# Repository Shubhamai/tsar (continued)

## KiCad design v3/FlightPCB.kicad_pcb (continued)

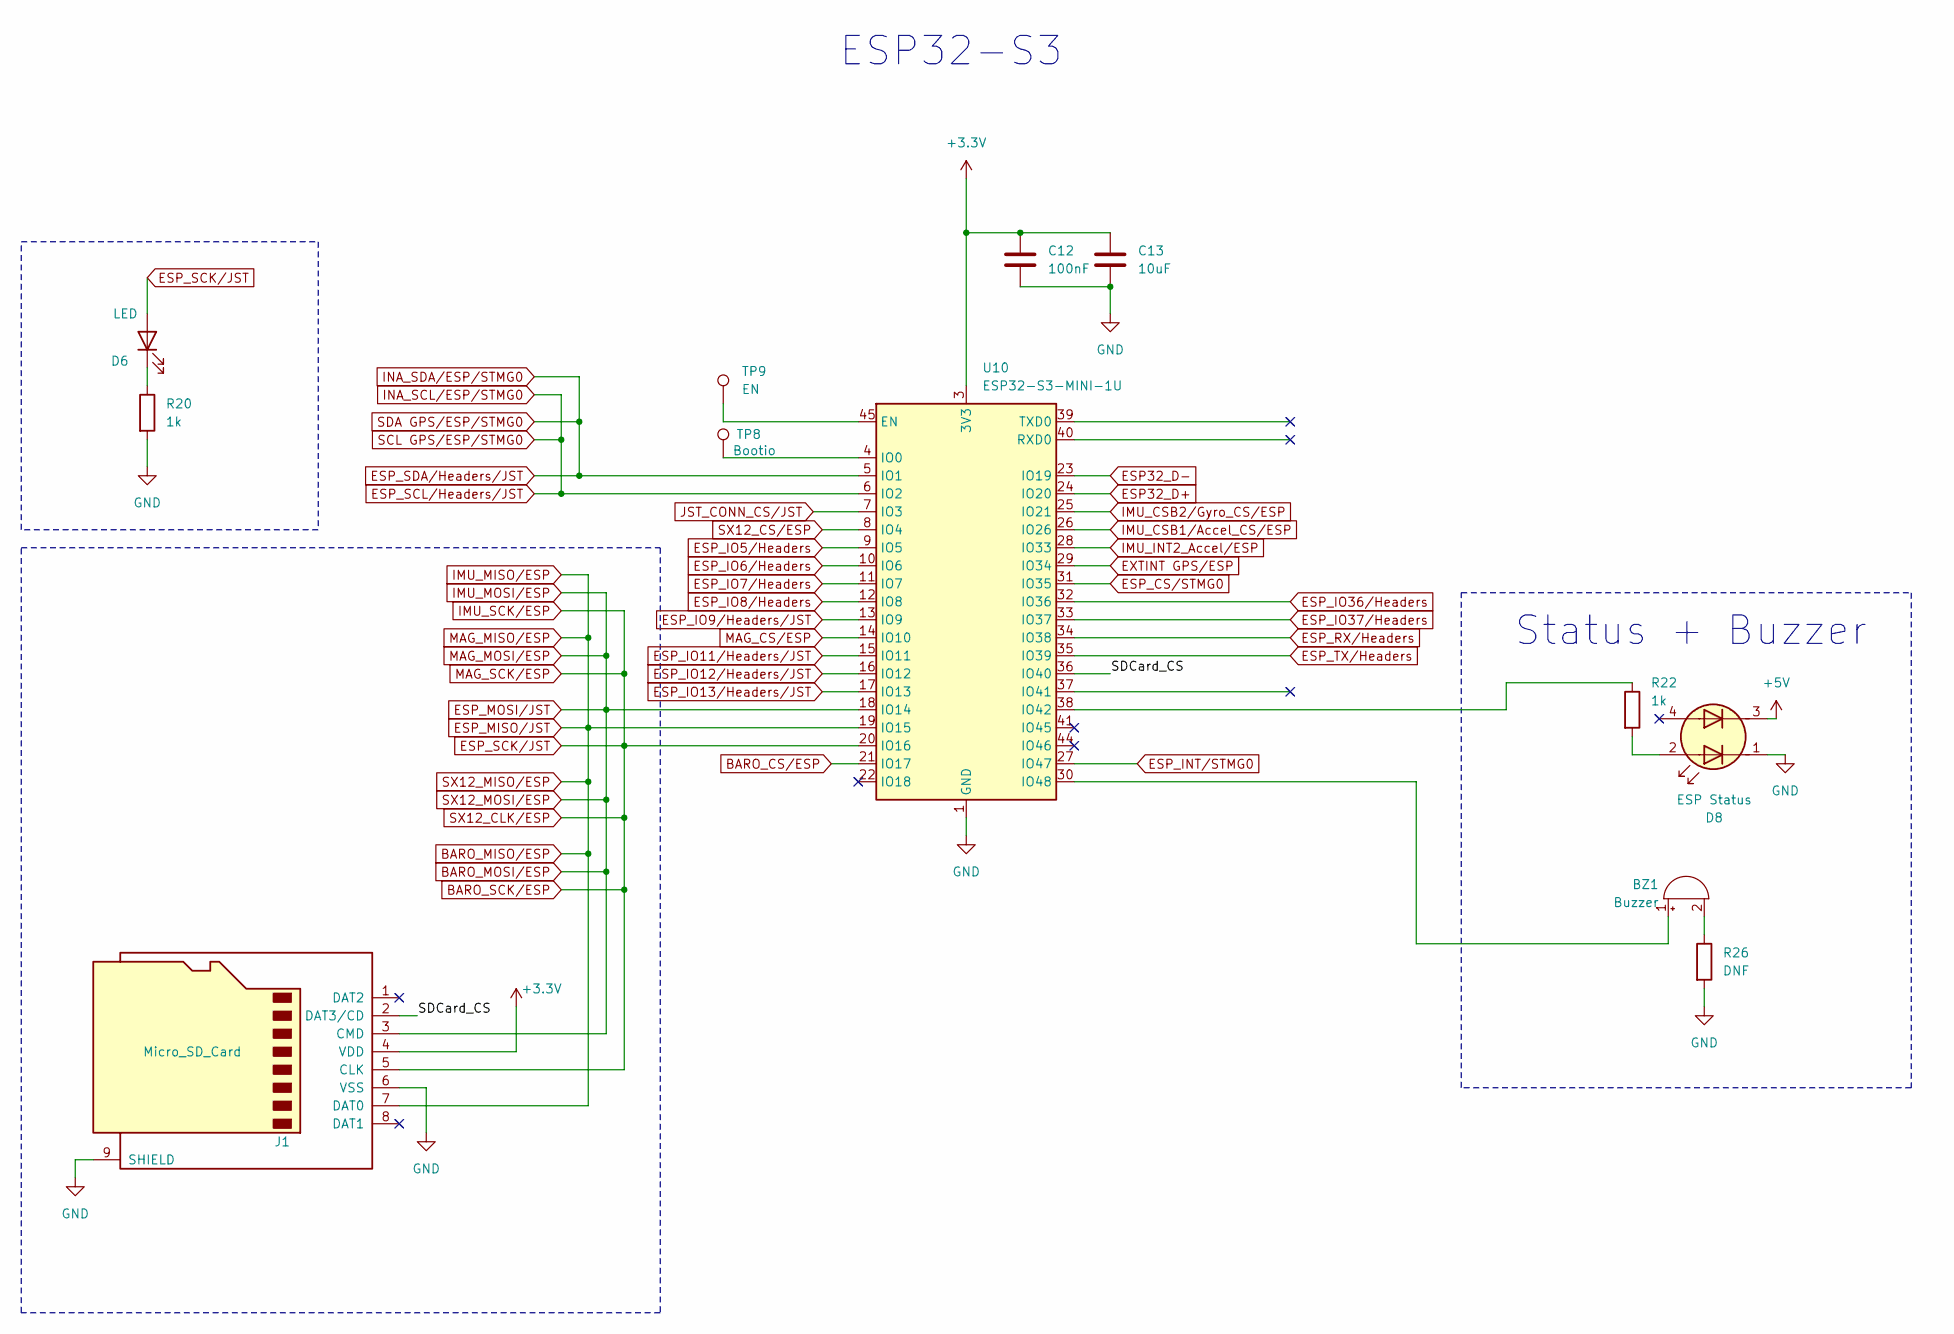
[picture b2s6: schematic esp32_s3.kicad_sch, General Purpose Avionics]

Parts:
BZ1: Buzzer; Buzzer_CUI_CPT-9019S-SMT
C12: 100nF; C_0603_1608Metric
C13: 10uF; C_0603_1608Metric
D6: LED; LED_0402_1005Metric
D8: ESP Status; IN-PI22TAT5R5G5B
J1: Micro_SD_Card; microSD_HC_Molex_47219-2001
R20, R22: 1k; R_0402_1005Metric
R26: DNF; R_0402_1005Metric
TP8: Bootio; TestPoint_Pad_D1.0mm
TP9: EN; TestPoint_Pad_D1.0mm
U10: ESP32-S3-MINI-1U; ESP32-S2-MINI-1U

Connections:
+3.3V: C12.1, C13.1, J1.4 (VDD), U10.3 (3V3); also elsewhere on the board
+5V: D8.3 (A2); also elsewhere on the board
/esp32_s3/SDCard_CS: J1.2 (DAT3/CD), U10.36 (IO40)
BARO_CS/ESP: U10.21 (IO17); also elsewhere on the board
BARO_MISO/ESP: J1.7 (DAT0), U10.19 (IO15); also elsewhere on the board
BARO_MOSI/ESP: J1.3 (CMD), U10.18 (IO14); also elsewhere on the board
BARO_SCK/ESP: D6.2 (A), J1.5 (CLK), U10.20 (IO16); also elsewhere on the board
BatteryTerminal-: C12.2, C13.2, D8.1 (A1), J1.6 (VSS), J1.9 (SHIELD), R20.2, R26.2, U10.1 (GND), U10.2 (GND), U10.42 (GND), U10.43 (GND), U10.46 (GND), U10.47 (GND), U10.48 (GND), U10.49 (GND), U10.50 (GND), U10.51 (GND), U10.52 (GND), U10.53 (GND), U10.54 (GND), U10.55 (GND), U10.56 (GND), U10.57 (GND), U10.58 (GND), U10.59 (GND), U10.60 (GND), U10.61 (GND), U10.62 (GND), U10.63 (GND), U10.64 (GND), U10.65 (GND); also elsewhere on the board
ESP32_D+: U10.24 (IO20); also elsewhere on the board
ESP32_D-: U10.23 (IO19); also elsewhere on the board
ESP_CS/STMG0: U10.31 (IO35); also elsewhere on the board
ESP_INT/STMG0: U10.27 (IO47); also elsewhere on the board
ESP_IO5/Headers: U10.9 (IO5); also elsewhere on the board
ESP_IO6/Headers: U10.10 (IO6); also elsewhere on the board
ESP_IO7/Headers: U10.11 (IO7); also elsewhere on the board
ESP_IO8/Headers: U10.12 (IO8); also elsewhere on the board
ESP_IO9/Headers/JST: U10.13 (IO9); also elsewhere on the board
ESP_IO11/Headers/JST: U10.15 (IO11); also elsewhere on the board
ESP_IO12/Headers/JST: U10.16 (IO12); also elsewhere on the board
ESP_IO13/Headers/JST: U10.17 (IO13); also elsewhere on the board
ESP_IO36/Headers: U10.32 (IO36); also elsewhere on the board
ESP_IO37/Headers: U10.33 (IO37); also elsewhere on the board
ESP_RX/Headers: U10.34 (IO38); also elsewhere on the board
ESP_SCL/Headers/JST: U10.6 (IO2); also elsewhere on the board
ESP_SDA/Headers/JST: U10.5 (IO1); also elsewhere on the board
ESP_TX/Headers: U10.35 (IO39); also elsewhere on the board
EXTINT GPS/ESP: U10.29 (IO34); also elsewhere on the board
IMU_CSB1/Accel_CS/ESP: U10.26 (IO26); also elsewhere on the board
IMU_CSB2/Gyro_CS/ESP: U10.25 (IO21); also elsewhere on the board
IMU_INT2_Accel/ESP: U10.28 (IO33); also elsewhere on the board
JST_CONN_CS/JST: U10.7 (IO3); also elsewhere on the board
MAG_CS/ESP: U10.14 (IO10); also elsewhere on the board
unnamed: BZ1.1 (+), U10.30 (IO48)
unnamed: BZ1.2 (-), R26.1
unnamed: D6.1 (K), R20.1
unnamed: D8.2 (K1), R22.2
unnamed: TP9.1, U10.45 (EN)
unnamed: TP8.1, U10.4 (IO0)
unnamed: R22.1, U10.38 (IO42)
SX12_CS/ESP: U10.8 (IO4); also elsewhere on the board

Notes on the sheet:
Status + Buzzer
ESP32-S3

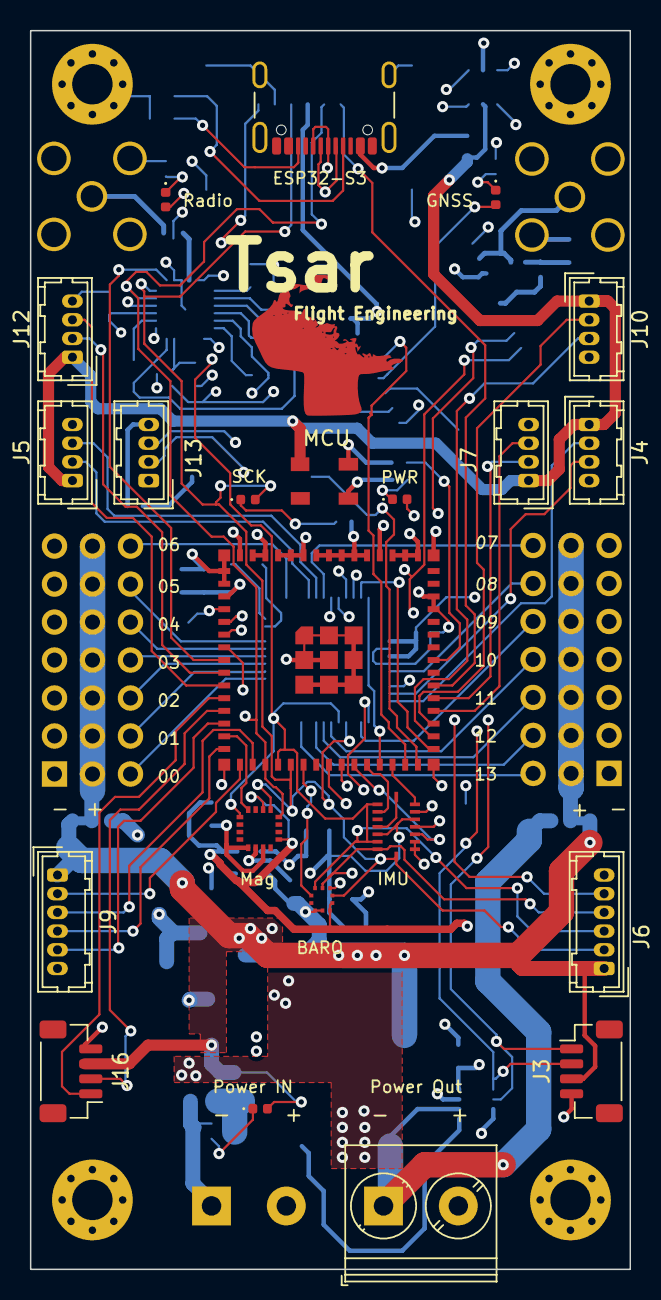
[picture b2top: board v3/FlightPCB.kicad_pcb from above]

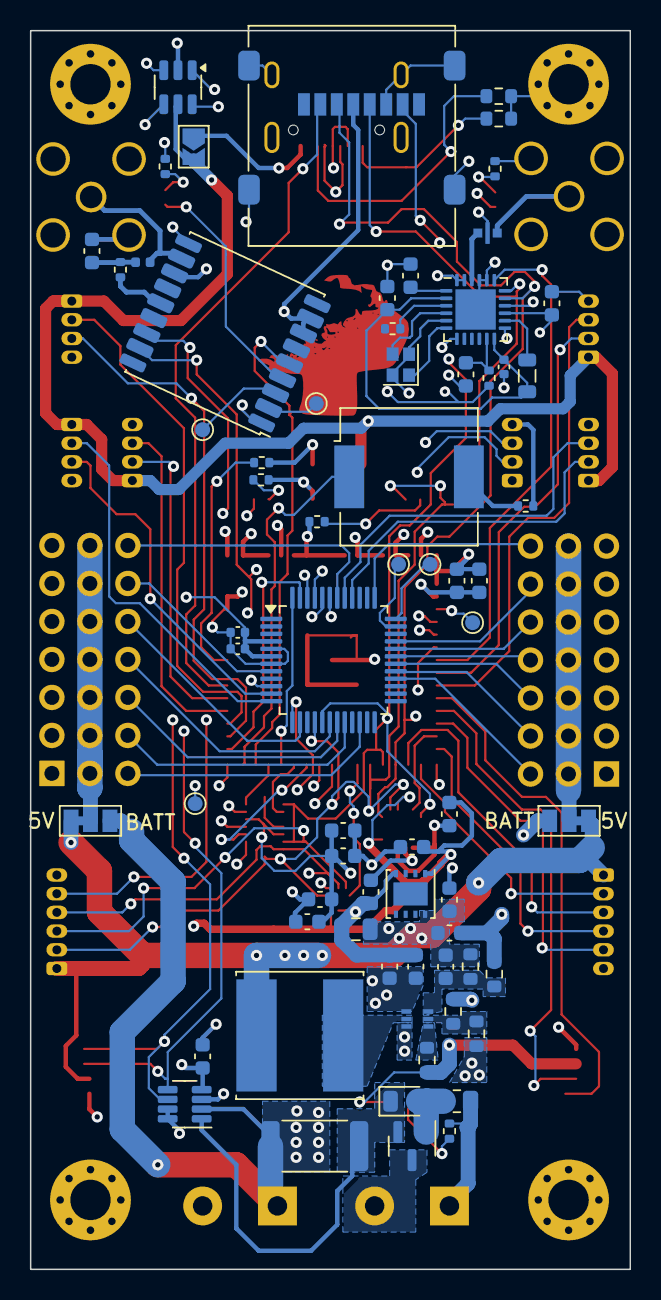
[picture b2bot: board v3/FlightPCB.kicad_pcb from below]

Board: 4 copper layers, 40.1 x 82.8 mm, 99 parts (68 on the bottom side), 99 nets.

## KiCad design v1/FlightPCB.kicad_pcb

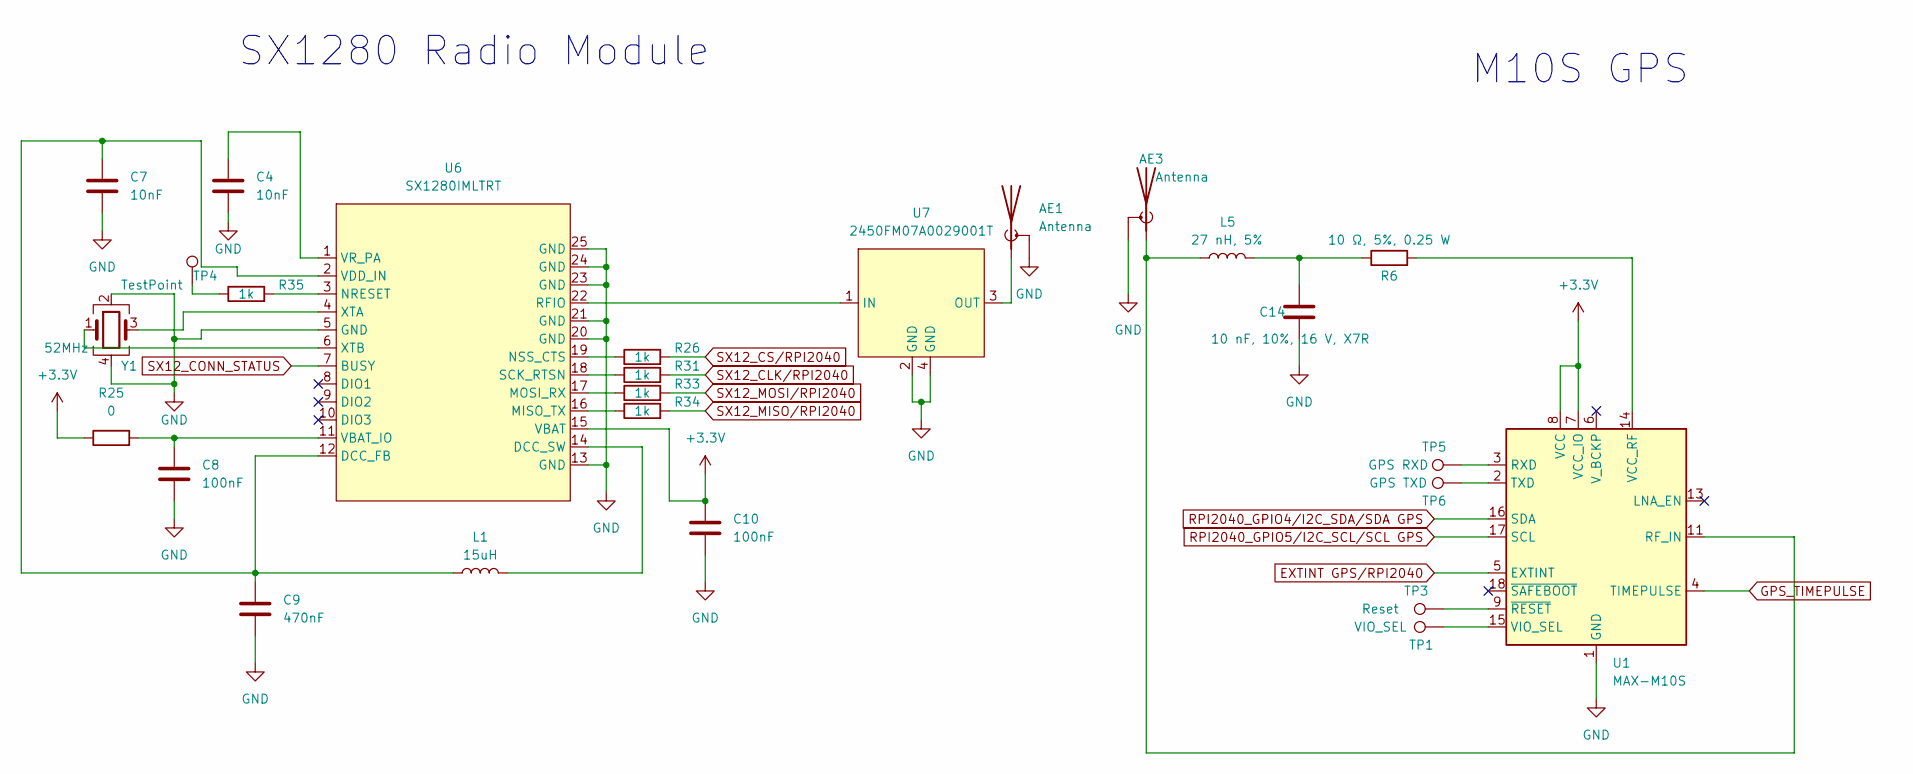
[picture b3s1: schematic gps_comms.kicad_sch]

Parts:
AE1, AE3: Antenna; SMA_Amphenol_901-144_Vertical
C4, C7: 10nF; C_0402_1005Metric
C8, C10: 100nF; C_0402_1005Metric
C9: 470nF; C_0402_1005Metric
C14: 10 nF, 10%, 16 V, X7R; C_0603_1608Metric
L1: 15uH; L_0805_2012Metric
L5: 27 nH, 5%; L_0402_1005Metric
R6: 10 Ω, 5%, 0.25 W; R_0402_1005Metric
R25: 0; R_0402_1005Metric
R26, R31, R33, R34, R35: 1k; R_0402_1005Metric
TP1: VIO_SEL; TestPoint_Pad_D1.0mm
TP3: Reset; TestPoint_Pad_D1.0mm
TP4: TestPoint; TestPoint_Pad_D1.0mm
TP5: GPS RXD; TestPoint_Pad_D1.0mm
TP6: GPS TXD; TestPoint_Pad_D1.0mm
U1: MAX-M10S; ublox_MAX
U6: SX1280IMLTRT; QFN-24-1EP_4x4mm_P0.5mm_EP2.7x2.7mm
U7: 2450FM07A0029001T
Y1: 52MHz; Crystal_SMD_2016-4Pin_2.0x1.6mm

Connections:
+3.3V: C10.1, R25.1, U1.7 (VCC_IO), U1.8 (VCC), U6.15 (VBAT); also elsewhere on the board
BatteryTerminal-: AE1.2 (Shield), AE3.2 (Shield), C4.2, C7.2, C8.2, C9.2, C10.2, C14.1, U1.1 (GND), U1.10 (GND), U1.12 (GND), U6.5 (GND), U6.13 (GND), U6.20 (GND), U6.21 (GND), U6.23 (GND), U6.24 (GND), U6.25 (GND), U7.2 (GND), U7.4 (GND), Y1.2, Y1.4; also elsewhere on the board
EXTINT GPS/RPI2040: U1.5 (EXTINT); also elsewhere on the board
GPS_TIMEPULSE: U1.4 (TIMEPULSE); also elsewhere on the board
INA_SCL_RPI2040: U1.17 (SCL); also elsewhere on the board
INA_SDA_RPI2040: U1.16 (SDA); also elsewhere on the board
unnamed: AE1.1 (A), U7.3 (OUT)
unnamed: AE3.1 (A), L5.1, U1.11 (RF_IN)
unnamed: C14.2, L5.2, R6.1
unnamed: R35.1, TP4.1
unnamed: TP5.1, U1.3 (RXD)
unnamed: TP6.1, U1.2 (TXD)
unnamed: R6.2, U1.14 (VCC_RF)
unnamed: TP1.1, U1.15 (VIO_SEL)
unnamed: TP3.1, U1.9 (~RESET)
unnamed: C7.1, C9.1, L1.1, U6.2 (VDD_IN), U6.12 (DCC_FB)
unnamed: L1.2, U6.14 (DCC_SW)
unnamed: R34.1, U6.16 (MISO_TX)
unnamed: R33.1, U6.17 (MOSI_RX)
unnamed: R35.2, U6.3 (NRESET)
unnamed: R26.1, U6.19 (NSS_CTS)
unnamed: U6.22 (RFIO), U7.1 (IN)
unnamed: R31.1, U6.18 (SCK_RTSN)
unnamed: C8.1, R25.2, U6.11 (VBAT_IO)
unnamed: C4.1, U6.1 (VR_PA)
unnamed: U6.4 (XTA), Y1.3
unnamed: U6.6 (XTB), Y1.1
RPI2040_GPIO16/MISO/SPI_PIN: R34.2; also elsewhere on the board
RPI2040_GPIO18/SCK/SPI_PIN: R31.2; also elsewhere on the board
RPI2040_GPIO19/MOSI/SPI_PIN: R33.2; also elsewhere on the board
SX12_CONN_STATUS: U6.7 (BUSY); also elsewhere on the board
SX12_CS/RPI2040: R26.2; also elsewhere on the board

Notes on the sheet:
M10S GPS
SX1280 Radio Module

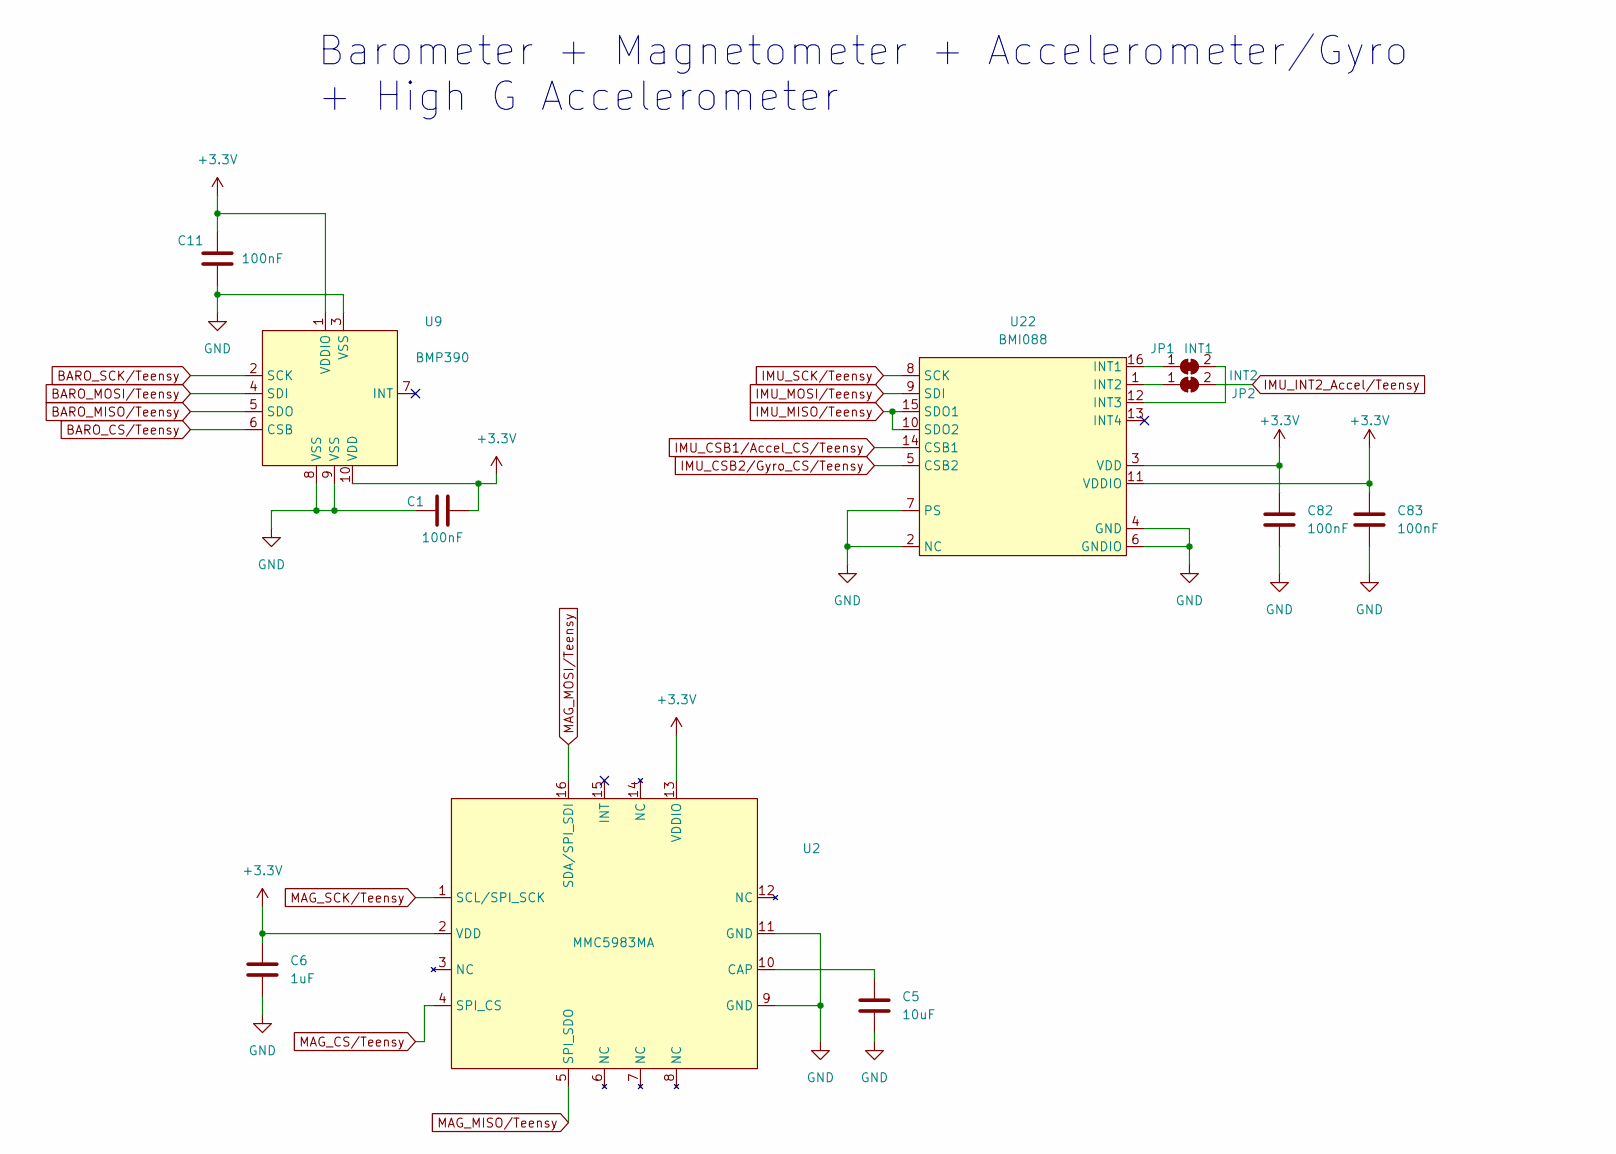
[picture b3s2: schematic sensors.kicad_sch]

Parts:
C1, C11, C82, C83: 100nF; C_0603_1608Metric
C5: 10uF; C_0805_2012Metric
C6: 1uF; C_0603_1608Metric
JP1: INT1; SolderJumper-2_P1.3mm_Bridged_Pad1.0x1.5mm
JP2: INT2; SolderJumper-2_P1.3mm_Bridged_Pad1.0x1.5mm
U2: MMC5983MA
U9: BMP390
U22: BMI088

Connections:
+3.3V: C1.2, C6.1, C11.2, C82.1, C83.1, U2.2 (VDD), U2.13 (VDDIO), U9.1 (VDDIO), U9.10 (VDD), U22.3 (VDD), U22.11 (VDDIO); also elsewhere on the board
BARO_CS/Teensy: U9.6 (CSB); also elsewhere on the board
BARO_MISO/Teensy: U2.5 (SPI_SDO), U9.5 (SDO), U22.10 (SDO2), U22.15 (SDO1); also elsewhere on the board
BARO_MOSI/Teensy: U2.16 (SDA/SPI_SDI), U9.4 (SDI), U22.9 (SDI); also elsewhere on the board
BARO_SCK/Teensy: U2.1 (SCL/SPI_SCK), U9.2 (SCK), U22.8 (SCK); also elsewhere on the board
BatteryTerminal-: C1.1, C5.2, C6.2, C11.1, C82.2, C83.2, U2.9 (GND), U2.11 (GND), U9.3 (VSS), U9.8 (VSS), U9.9 (VSS), U22.2 (NC), U22.4 (GND), U22.6 (GNDIO), U22.7 (PS); also elsewhere on the board
IMU_CSB1/Accel_CS/Teensy: U22.14 (CSB1); also elsewhere on the board
IMU_CSB2/Gyro_CS/Teensy: U22.5 (CSB2); also elsewhere on the board
IMU_INT2_Accel/Teensy: JP2.2 (B); also elsewhere on the board
MAG_CS/Teensy: U2.4 (SPI_CS); also elsewhere on the board
unnamed: JP1.1 (A), U22.16 (INT1)
unnamed: JP1.2 (B), U22.12 (INT3)
unnamed: JP2.1 (A), U22.1 (INT2)
unnamed: C5.1, U2.10 (CAP)

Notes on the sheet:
Barometer + Magnetometer + Accelerometer/Gyro + High G Accelerometer

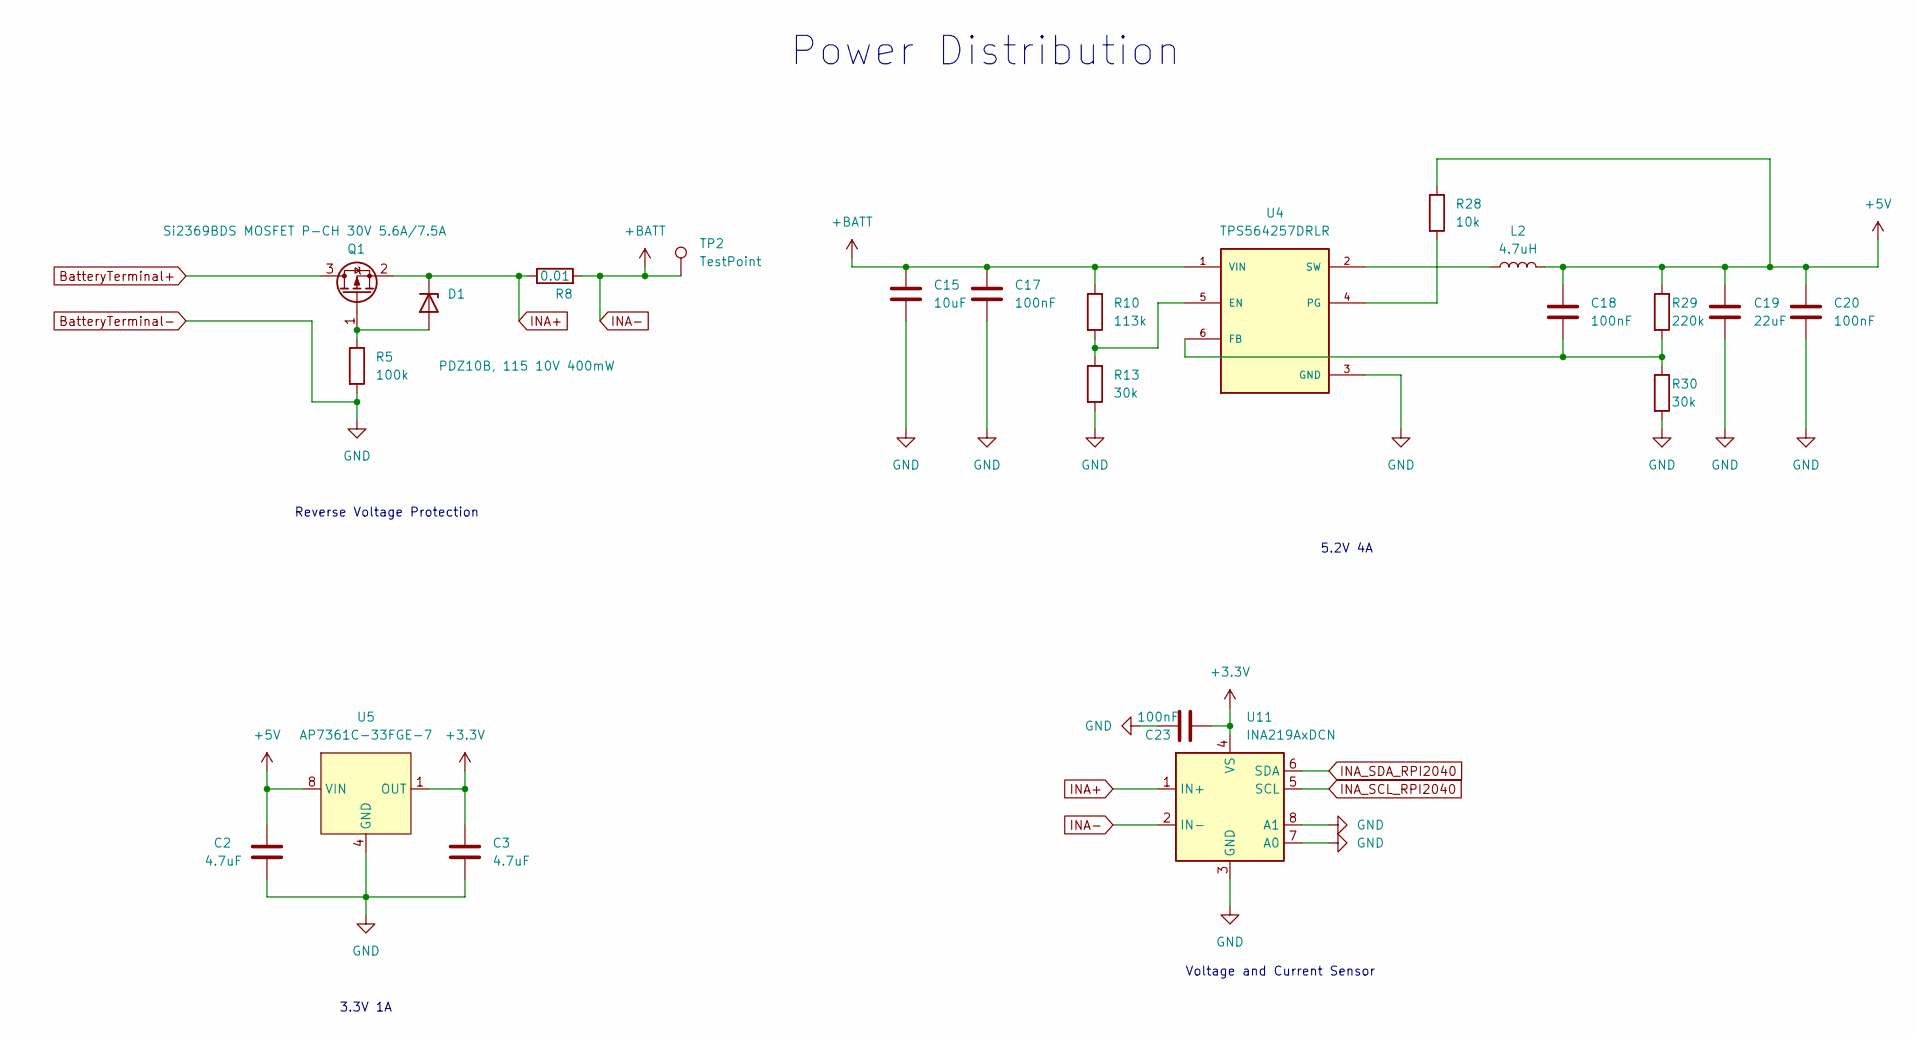
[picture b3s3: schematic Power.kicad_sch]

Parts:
C2, C3: 4.7uF; C_0603_1608Metric
C15: 10uF; C_0805_2012Metric
C17, C18, C20, C23: 100nF; C_0603_1608Metric
C19: 22uF; C_0805_2012Metric
D1: PDZ10B, 115 10V 400mW; D_0805_2012Metric
L2: 4.7uH; L_0805_2012Metric
Q1: Si2369BDS MOSFET P-CH 30V 5.6A/7.5A; SOT-23
R5: 100k; R_0805_2012Metric
R8: 0.01; R_2512_6332Metric
R10: 113k; R_0603_1608Metric
R13, R30: 30k; R_0603_1608Metric
R28: 10k; R_0603_1608Metric
R29: 220k; R_0603_1608Metric
TP2: TestPoint; TestPoint_Pad_D1.0mm
U4: TPS564257DRLR; SOT50P160X60-6N; PARTREV A
U5: AP7361C-33FGE-7; MLF-8-1EP_3x3mm_P0.65mm_EP1.55x2.3mm
U11: INA219AxDCN; SOT-23-8

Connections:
+3.3V: C3.1, C23.2, U5.1 (OUT), U11.4 (VS); also elsewhere on the board
+5V: C2.1, C18.1, C19.1, C20.1, L2.2, R28.1, R29.1, U5.8 (VIN); also elsewhere on the board
BatteryTerminal+: Q1.3 (D); also elsewhere on the board
BatteryTerminal-: C2.2, C3.2, C15.2, C17.2, C19.2, C20.2, C23.1, R5.2, R13.2, R30.2, U4.3 (GND), U5.4 (GND), U11.3 (GND), U11.7 (A0), U11.8 (A1); also elsewhere on the board
INA+: D1.1 (K), Q1.2 (S), R8.1, U11.1 (IN+)
INA-: C15.1, C17.1, R8.2, R10.1, TP2.1, U4.1 (VIN), U11.2 (IN-)
INA_SCL_RPI2040: U11.5 (SCL); also elsewhere on the board
INA_SDA_RPI2040: U11.6 (SDA); also elsewhere on the board
unnamed: D1.2 (A), Q1.1 (G), R5.1
unnamed: R10.2, R13.1, U4.5 (EN)
unnamed: C18.2, R29.2, R30.1, U4.6 (FB)
unnamed: R28.2, U4.4 (PG)
unnamed: L2.1, U4.2 (SW)

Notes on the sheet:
Voltage and Current Sensor
3.3V 1A
Reverse Voltage Protection
5.2V 4A
Power Distribution

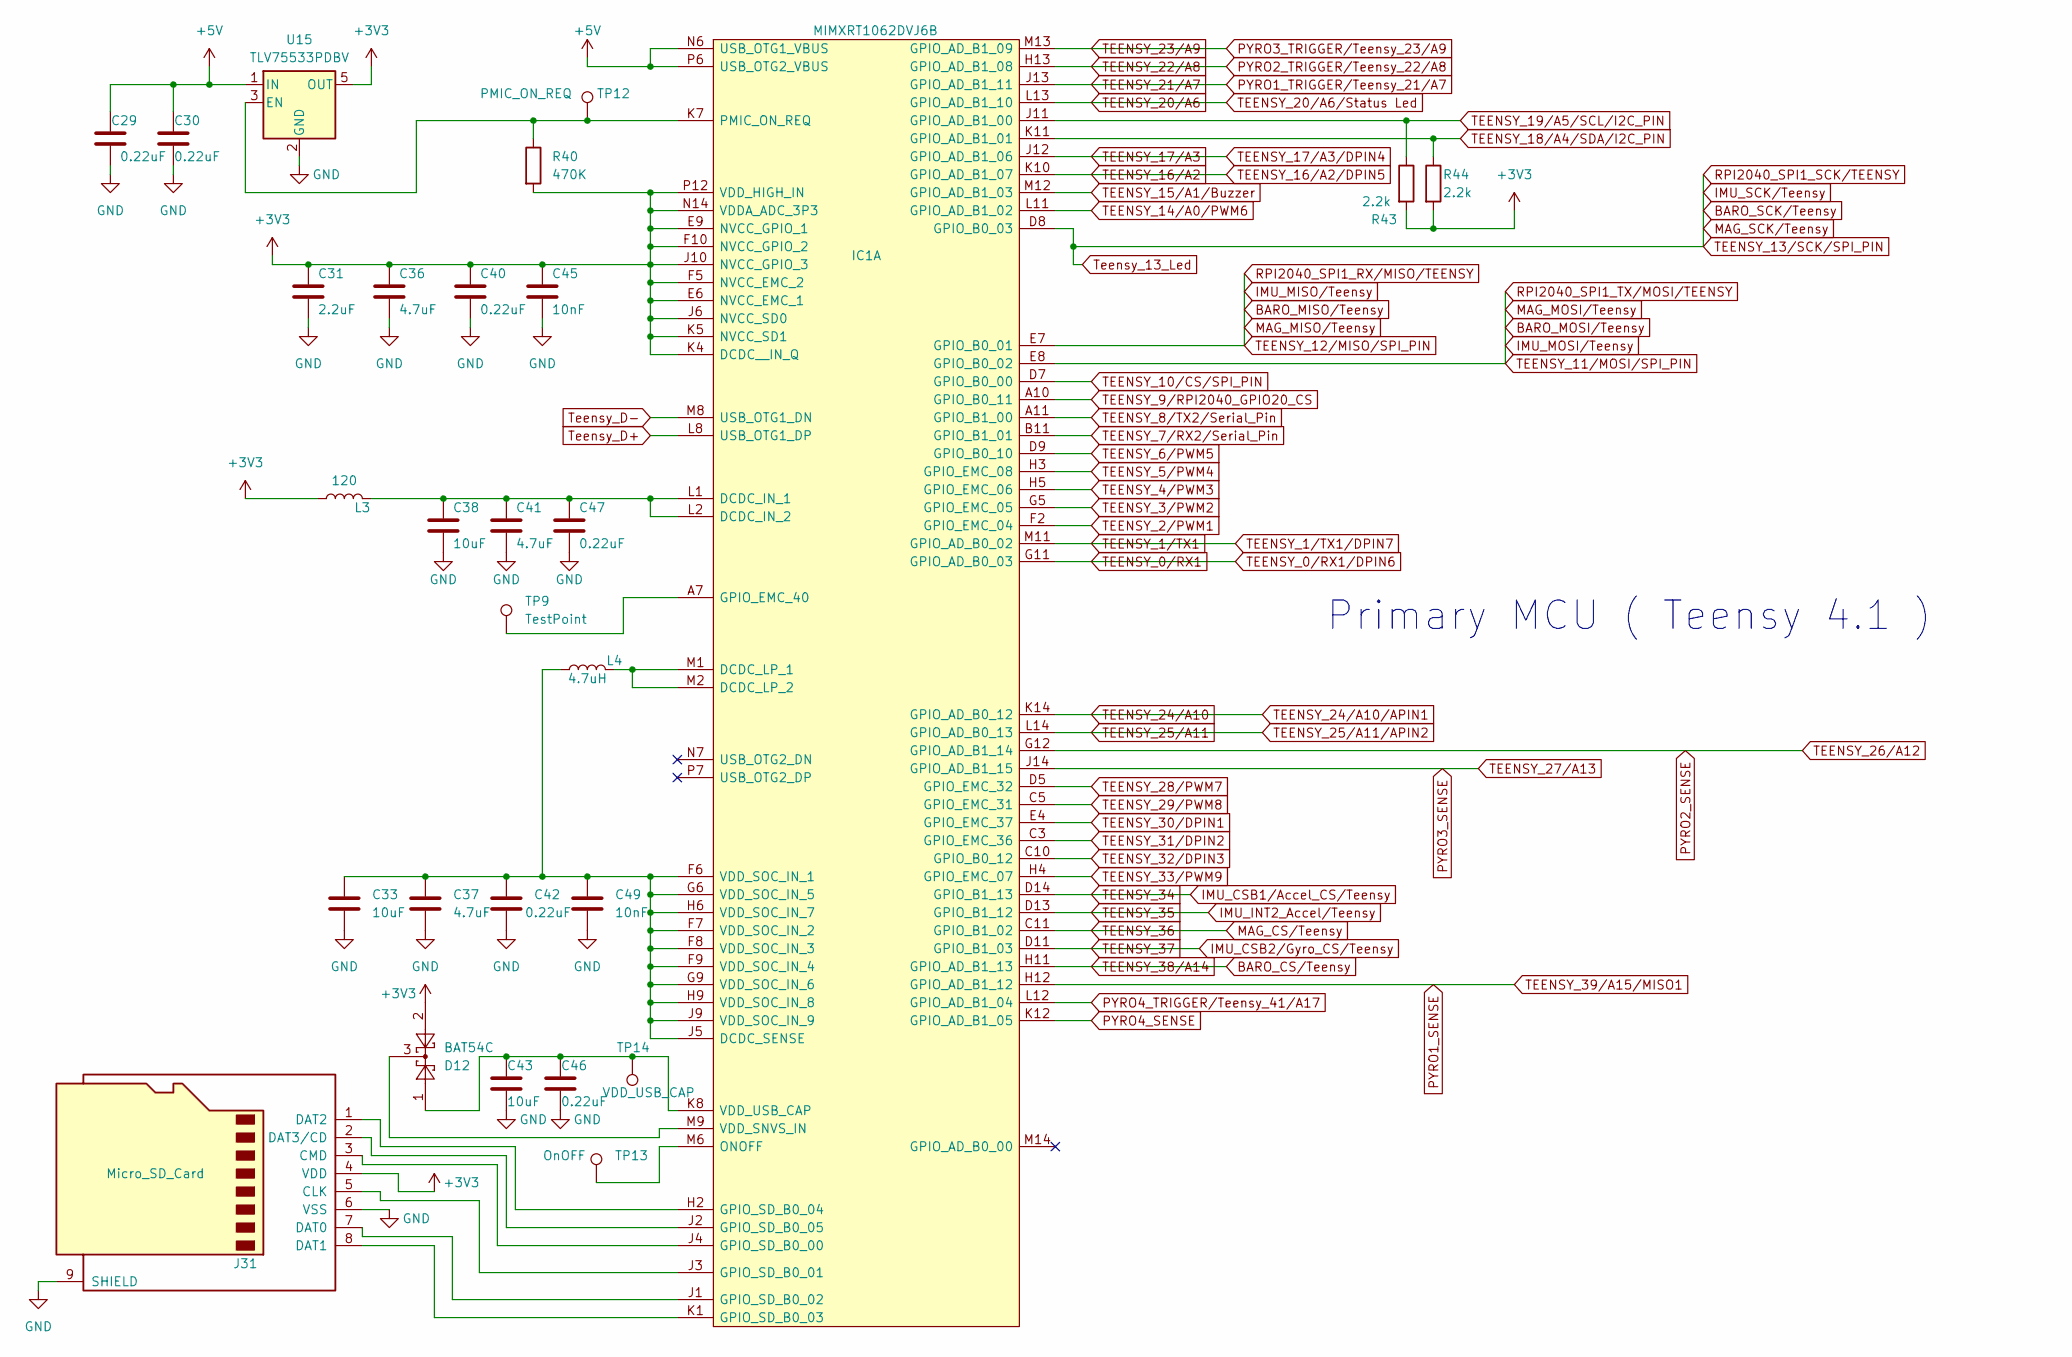
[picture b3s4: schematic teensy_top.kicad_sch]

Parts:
C29, C30, C40, C42, C46, C47: 0.22uF; C_0402_1005Metric
C31: 2.2uF; C_0603_1608Metric
C33, C38, C43: 10uF; C_0603_1608Metric
C36, C37, C41: 4.7uF; C_0603_1608Metric
C45, C49: 10nF; C_0402_1005Metric
D12: BAT54C; SOT-23
IC1: MIMXRT1062DVJ6B; BGA196C80P14X14_1200X1200X152; Mouser Part Number 771-MIMXRT1062DVJ6B
J31: Micro_SD_Card; microSD_HC_Molex_47219-2001
L3: 120; L_0805_2012Metric
L4: 4.7uH; L_0805_2012Metric
R40: 470K; R_0603_1608Metric
R43, R44: 2.2k; R_0603_1608Metric
TP9: TestPoint; TestPoint_Pad_D1.0mm
TP12: PMIC_ON_REQ; TestPoint_Pad_D1.0mm
TP13: OnOFF; TestPoint_Pad_D1.0mm
TP14: VDD_USB_CAP; TestPoint_Pad_D1.0mm
U15: TLV75533PDBV; SOT-23-5

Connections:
+5V: C29.1, C30.1, IC1.N6 (USB_OTG1_VBUS), IC1.P6 (USB_OTG2_VBUS), U15.1 (IN); also elsewhere on the board
BARO_CS/Teensy: IC1.H11 (GPIO_AD_B1_13); also elsewhere on the board
BARO_MISO/Teensy: IC1.E7 (GPIO_B0_01); also elsewhere on the board
BARO_MOSI/Teensy: IC1.E8 (GPIO_B0_02); also elsewhere on the board
BARO_SCK/Teensy: IC1.D8 (GPIO_B0_03); also elsewhere on the board
BatteryTerminal-: C29.2, C30.2, C31.2, C33.2, C36.2, C37.2, C38.2, C40.2, C41.2, C42.2, C43.2, C45.2, C46.2, C47.2, C49.2, J31.6 (VSS), J31.9 (SHIELD), U15.2 (GND); also elsewhere on the board
IMU_CSB1/Accel_CS/Teensy: IC1.D14 (GPIO_B1_13); also elsewhere on the board
IMU_CSB2/Gyro_CS/Teensy: IC1.D11 (GPIO_B1_03); also elsewhere on the board
IMU_INT2_Accel/Teensy: IC1.D13 (GPIO_B1_12); also elsewhere on the board
MAG_CS/Teensy: IC1.C11 (GPIO_B1_02); also elsewhere on the board
unnamed: C38.1, C41.1, C47.1, IC1.L1 (DCDC_IN_1), IC1.L2 (DCDC_IN_2), L3.1
unnamed: IC1.M1 (DCDC_LP_1), IC1.M2 (DCDC_LP_2), L4.2
unnamed: C33.1, C37.1, C42.1, C49.1, IC1.F6 (VDD_SOC_IN_1), IC1.F7 (VDD_SOC_IN_2), IC1.F8 (VDD_SOC_IN_3), IC1.F9 (VDD_SOC_IN_4), IC1.G6 (VDD_SOC_IN_5), IC1.G9 (VDD_SOC_IN_6), IC1.H6 (VDD_SOC_IN_7), IC1.H9 (VDD_SOC_IN_8), IC1.J5 (DCDC_SENSE), IC1.J9 (VDD_SOC_IN_9), L4.1
unnamed: IC1.A7 (GPIO_EMC_40), TP9.1
unnamed: IC1.J4 (GPIO_SD_B0_00), J31.3 (CMD)
unnamed: IC1.J3 (GPIO_SD_B0_01), J31.5 (CLK)
unnamed: IC1.J1 (GPIO_SD_B0_02), J31.7 (DAT0)
unnamed: IC1.K1 (GPIO_SD_B0_03), J31.8 (DAT1)
unnamed: IC1.H2 (GPIO_SD_B0_04), J31.1 (DAT2)
unnamed: IC1.J2 (GPIO_SD_B0_05), J31.2 (DAT3/CD)
unnamed: IC1.M6 (ONOFF), TP13.1
unnamed: IC1.K7 (PMIC_ON_REQ), R40.1, TP12.1, U15.3 (EN)
unnamed: D12.3, IC1.M9 (VDD_SNVS_IN)
unnamed: C43.1, C46.1, D12.1, IC1.K8 (VDD_USB_CAP), TP14.1
PYRO1_SENSE: IC1.H12 (GPIO_AD_B1_12); also elsewhere on the board
PYRO1_TRIGGER/Teensy_21/A7: IC1.J13 (GPIO_AD_B1_11); also elsewhere on the board
PYRO2_SENSE: IC1.G12 (GPIO_AD_B1_14); also elsewhere on the board
PYRO2_TRIGGER/Teensy_22/A8: IC1.H13 (GPIO_AD_B1_08); also elsewhere on the board
PYRO3_SENSE: IC1.J14 (GPIO_AD_B1_15); also elsewhere on the board
PYRO3_TRIGGER/Teensy_23/A9: IC1.M13 (GPIO_AD_B1_09); also elsewhere on the board
PYRO4_SENSE: IC1.K12 (GPIO_AD_B1_05); also elsewhere on the board
PYRO4_TRIGGER/Teensy_41/A17: IC1.L12 (GPIO_AD_B1_04); also elsewhere on the board
TEENSY_0/RX1: IC1.G11 (GPIO_AD_B0_03); also elsewhere on the board
TEENSY_1/TX1: IC1.M11 (GPIO_AD_B0_02); also elsewhere on the board
TEENSY_2/PWM1: IC1.F2 (GPIO_EMC_04); also elsewhere on the board
TEENSY_3/PWM2: IC1.G5 (GPIO_EMC_05); also elsewhere on the board
TEENSY_4/PWM3: IC1.H5 (GPIO_EMC_06); also elsewhere on the board
TEENSY_5/PWM4: IC1.H3 (GPIO_EMC_08); also elsewhere on the board
TEENSY_6/PWM5: IC1.D9 (GPIO_B0_10); also elsewhere on the board
TEENSY_7/RX2/Serial_Pin: IC1.B11 (GPIO_B1_01); also elsewhere on the board
TEENSY_8/TX2/Serial_Pin: IC1.A11 (GPIO_B1_00); also elsewhere on the board
TEENSY_9/RPI2040_GPIO20_CS: IC1.A10 (GPIO_B0_11); also elsewhere on the board
TEENSY_10/CS/SPI_PIN: IC1.D7 (GPIO_B0_00); also elsewhere on the board
TEENSY_14/A0/PWM6: IC1.L11 (GPIO_AD_B1_02); also elsewhere on the board
TEENSY_15/A1/Buzzer: IC1.M12 (GPIO_AD_B1_03); also elsewhere on the board
TEENSY_16/A2: IC1.K10 (GPIO_AD_B1_07); also elsewhere on the board
TEENSY_17/A3: IC1.J12 (GPIO_AD_B1_06); also elsewhere on the board
TEENSY_18/A4/SDA/I2C_PIN: IC1.K11 (GPIO_AD_B1_01), R44.1; also elsewhere on the board
TEENSY_19/A5/SCL/I2C_PIN: IC1.J11 (GPIO_AD_B1_00), R43.1; also elsewhere on the board
TEENSY_20/A6: IC1.L13 (GPIO_AD_B1_10); also elsewhere on the board
TEENSY_24/A10: IC1.K14 (GPIO_AD_B0_12); also elsewhere on the board
TEENSY_25/A11: IC1.L14 (GPIO_AD_B0_13); also elsewhere on the board
TEENSY_28/PWM7: IC1.D5 (GPIO_EMC_32); also elsewhere on the board
TEENSY_29/PWM8: IC1.C5 (GPIO_EMC_31); also elsewhere on the board
TEENSY_30/DPIN1: IC1.E4 (GPIO_EMC_37); also elsewhere on the board
TEENSY_31/DPIN2: IC1.C3 (GPIO_EMC_36); also elsewhere on the board
TEENSY_32/DPIN3: IC1.C10 (GPIO_B0_12); also elsewhere on the board
TEENSY_33/PWM9: IC1.H4 (GPIO_EMC_07); also elsewhere on the board
Teensy_D+: IC1.L8 (USB_OTG1_DP); also elsewhere on the board
Teensy_D-: IC1.M8 (USB_OTG1_DN); also elsewhere on the board
W25Q_VDD_LED: C31.1, C36.1, C40.1, C45.1, D12.2, IC1.E6 (NVCC_EMC_1), IC1.E9 (NVCC_GPIO_1), IC1.F5 (NVCC_EMC_2), IC1.F10 (NVCC_GPIO_2), IC1.J6 (NVCC_SD0), IC1.J10 (NVCC_GPIO_3), IC1.K4 (DCDC__IN_Q), IC1.K5 (NVCC_SD1), IC1.N14 (VDDA_ADC_3P3), IC1.P12 (VDD_HIGH_IN), J31.4 (VDD), L3.2, R40.2, R43.2, R44.2, U15.5 (OUT); also elsewhere on the board

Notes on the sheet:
Primary MCU ( Teensy 4.1 )
